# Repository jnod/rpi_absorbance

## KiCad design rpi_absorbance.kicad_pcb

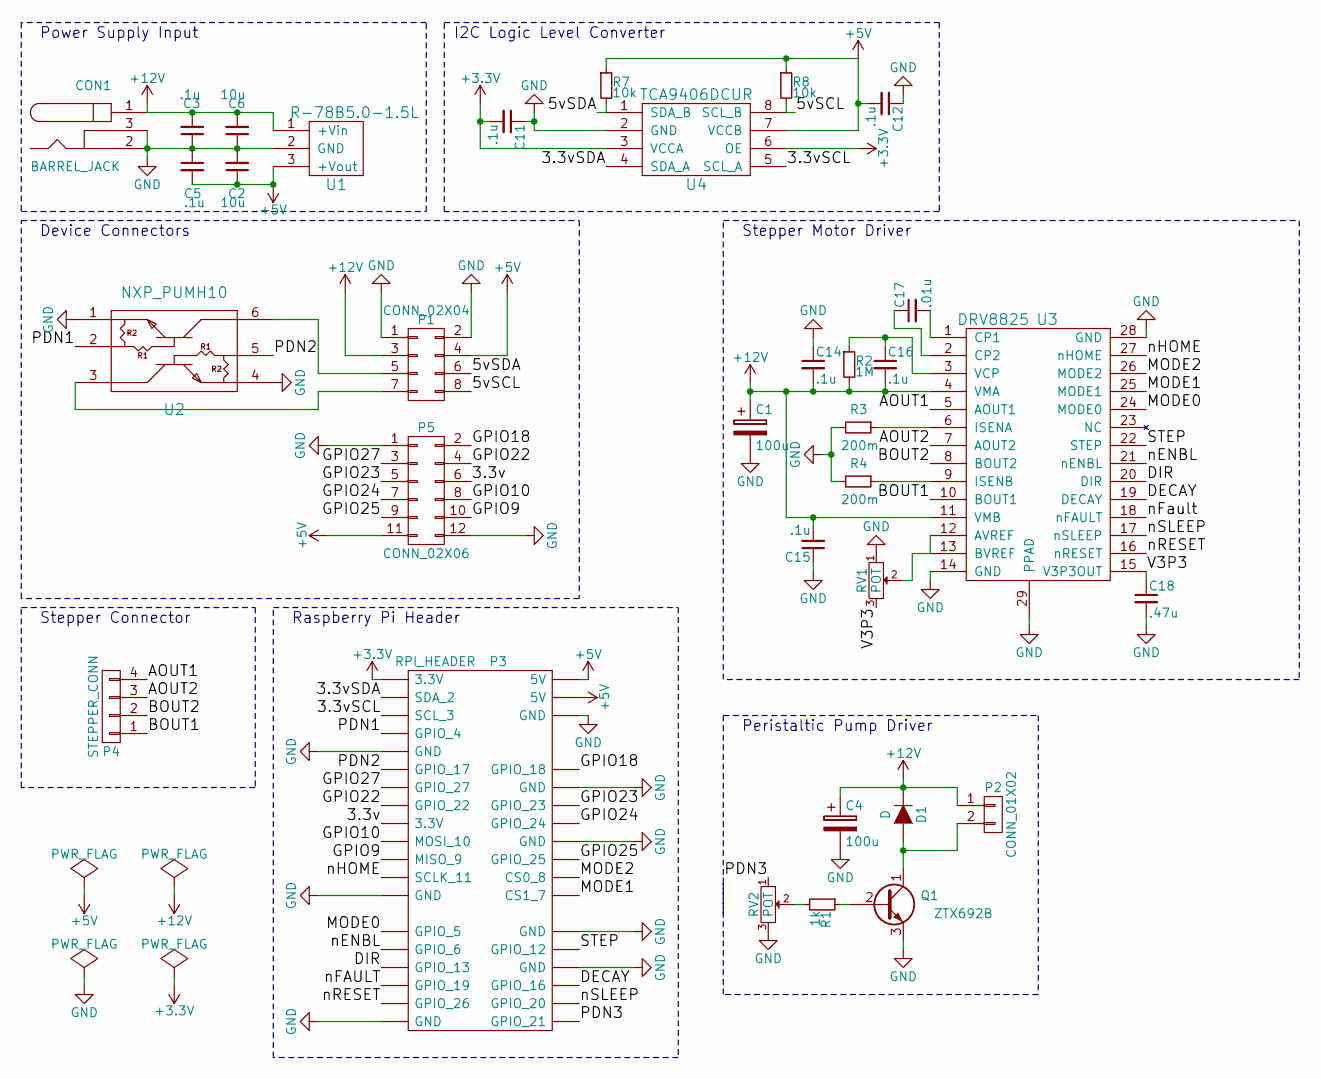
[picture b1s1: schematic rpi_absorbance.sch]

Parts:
C1, C4: 100u; C_Radial_D6.3_L11.2_P2.5
C2, C6: 10u; C_0603
C3, C5, C11, C12, C14, C15, C16: .1u; C_0603
C17: .01u; C_0603
C18: .47u; C_0603
CON1: BARREL_JACK; CUI_PJ-002AH-SMT
D1: D; SOD-123
P1: CONN_02X04; Pin_Header_Straight_2x04
P2: CONN_01X02; Pin_Header_Straight_1x02
P3: RPI_HEADER; Pin_Header_Straight_2x20
P4: STEPPER_CONN; Pin_Header_Straight_1x04
P5: CONN_02X06; Pin_Header_Straight_2x06
Q1: ZTX692B; TO-92_Inline_Narrow_Oval
R1: 1k; R_0805_HandSoldering
R2: 1M; R_0603
R3, R4: 200m; R_0603
R7, R8: 10k; R_0805_HandSoldering
RV1, RV2: POT; BOURNS_TC33
U1: R-78B5.0-1.5L; R-78B-3-SIP
U2: NXP_PUMH10; SOT−363
U3: DRV8825; 28-HTSSOP
U4: TCA9406DCUR; 8-VSSOP

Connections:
+3V3: C11.2, P3.1 (3.3V), U4.3 (VCCA), U4.6 (OE)
+5V: C2.1, C5.2, C12.2, P1.4, P3.2 (5V), P3.4 (5V), P5.11, R7.1, R8.1, U1.3 (+Vout), U4.7 (VCCB)
+12V: C1.1, C3.2, C4.1, C6.2, C14.2, C15.2, C16.2, CON1.1, D1.1 (K), P1.3, P2.1, R2.2, U1.1 (+Vin), U3.4 (VMA), U3.11 (VMB)
/3.3v: P3.17 (3.3V), P5.6
/3.3vSCL: P3.5 (SCL_3), U4.5 (SCL_A)
/3.3vSDA: P3.3 (SDA_2), U4.4 (SDA_A)
/5vSCL: P1.8, R8.2, U4.8 (SCL_B)
/5vSDA: P1.6, R7.2, U4.1 (SDA_B)
/AOUT1: P4.4, U3.5 (AOUT1)
/AOUT2: P4.3, U3.7 (AOUT2)
/BOUT1: P4.1, U3.10 (BOUT1)
/BOUT2: P4.2, U3.8 (BOUT2)
/DECAY: P3.36 (GPIO_16), U3.19 (DECAY)
/DIR: P3.33 (GPIO_13), U3.20 (DIR)
/GPIO9: P3.21 (MISO_9), P5.10
/GPIO10: P3.19 (MOSI_10), P5.8
/GPIO18: P3.12 (GPIO_18), P5.2
/GPIO22: P3.15 (GPIO_22), P5.4
/GPIO23: P3.16 (GPIO_23), P5.5
/GPIO24: P3.18 (GPIO_24), P5.7
/GPIO25: P3.22 (GPIO_25), P5.9
/GPIO27: P3.13 (GPIO_27), P5.3
/MODE0: P3.29 (GPIO_5), U3.24 (MODE0)
/MODE1: P3.26 (CS1_7), U3.25 (MODE1)
/MODE2: P3.24 (CS0_8), U3.26 (MODE2)
/PDN1: P3.7 (GPIO_4), U2.2
/PDN2: P3.11 (GPIO_17), U2.5
/PDN3: P3.40 (GPIO_21), RV2.1
/STEP: P3.32 (GPIO_12), U3.22 (STEP)
/V3P3: C18.1, RV1.3, U3.15 (V3P3OUT)
/nENBL: P3.31 (GPIO_6), U3.21 (nENBL)
/nFAULT: P3.35 (GPIO_19), U3.18 (nFAULT)
/nHOME: P3.23 (SCLK_11), U3.27 (nHOME)
/nRESET: P3.37 (GPIO_26), U3.16 (nRESET)
/nSLEEP: P3.38 (GPIO_20), U3.17 (nSLEEP)
GND: C1.2, C2.2, C3.1, C4.2, C5.1, C6.1, C11.1, C12.1, C14.1, C15.1, C18.2, CON1.2, CON1.3, P1.1, P1.2, P3.6 (GND), P3.9 (GND), P3.14 (GND), P3.20 (GND), P3.25 (GND), P3.30 (GND), P3.34 (GND), P3.39 (GND), P5.1, P5.12, Q1.3 (E), R3.2, R4.2, RV1.1, RV2.3, U1.2 (GND), U2.1, U2.4, U3.14 (GND), U3.28 (GND), U3.29 (PPAD), U4.2 (GND)
unnamed: C16.1, R2.1, U3.3 (VCP)
unnamed: C17.1, U3.2 (CP2)
unnamed: C17.2, U3.1 (CP1)
unnamed: D1.2 (A), P2.2, Q1.1 (C)
unnamed: P1.5, U2.6
unnamed: P1.7, U2.3
unnamed: Q1.2 (B), R1.1
unnamed: R1.2, RV2.2
unnamed: R3.1, U3.6 (ISENA)
unnamed: R4.1, U3.9 (ISENB)
unnamed: RV1.2, U3.12 (AVREF), U3.13 (BVREF)

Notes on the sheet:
Power Supply Input
I2C Logic Level Converter
Stepper Connector
Stepper Motor Driver
Raspberry Pi Header
Device Connectors
Peristaltic Pump Driver

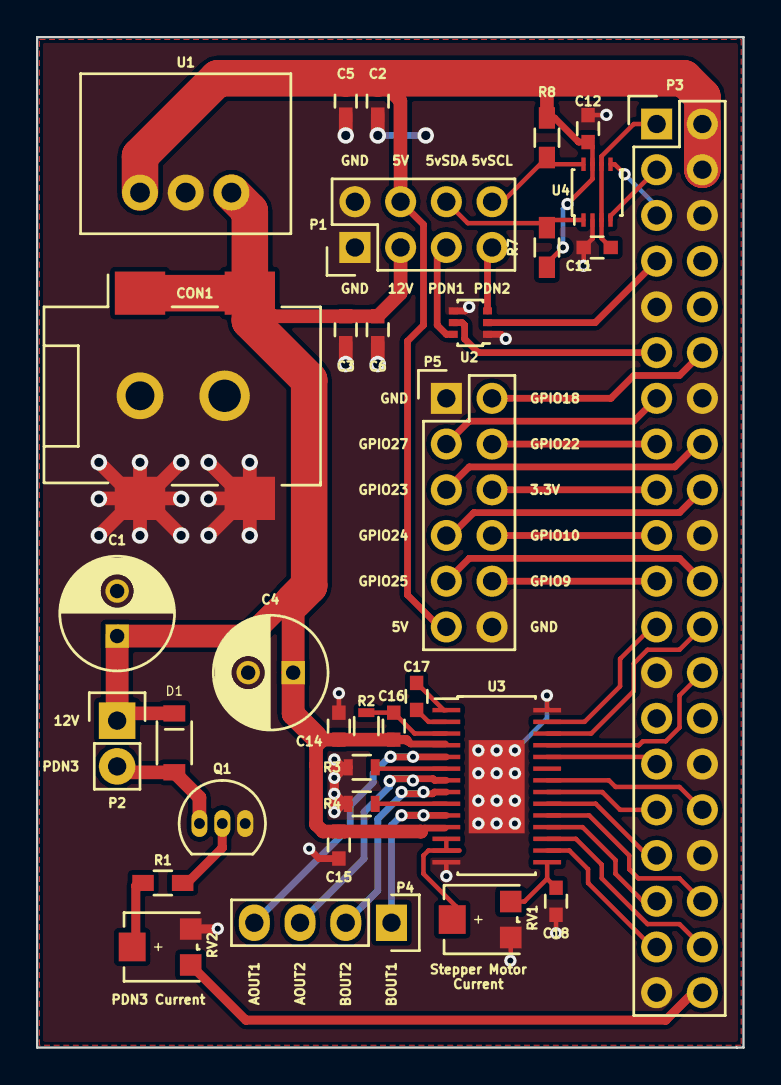
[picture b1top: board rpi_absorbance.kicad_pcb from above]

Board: 2 copper layers, 39.2 x 56.1 mm, 33 parts (0 on the bottom side), 47 nets.

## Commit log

2016-02-23 Add existing files
2016-02-23 Add stepper driver circuit
2016-02-23 Connect raspberry pi header
2016-02-23 Add components
2016-02-24 Add footprints
2016-02-24 Start pcb layout
2016-02-27 Revise circuit
2016-02-29 Add transistors
2016-02-29 Update footprints
2016-02-29 Update layout
2016-02-29 Complete stepper driver circuit
2016-02-29 Reorganize pcb
2016-03-01 Change potentiometer footprint
2016-03-01 Improve pcb layout, change capacitor footprints
2016-03-01 Add LED transistor layout
2016-03-01 Start connecting gpio header
2016-03-01 Add labels and outline
2016-03-01 Add missing connections
2016-03-02 Replace power input footprint
2016-03-02 Add gitignore for gerber files
2016-03-02 Remove gerber files
2016-03-02 Modify .gitignore
2016-03-02 Replace 2xNPN transistor
2016-03-03 Reorganize project
2016-03-04 Update silk screen
2016-03-04 Update resistors
2016-03-06 Update pcb
2016-03-09 Move vias
